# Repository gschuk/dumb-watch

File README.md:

# dumb-watch
Exercise Lab of Lecture Advanced PCB Design @ TU Darmstadt.

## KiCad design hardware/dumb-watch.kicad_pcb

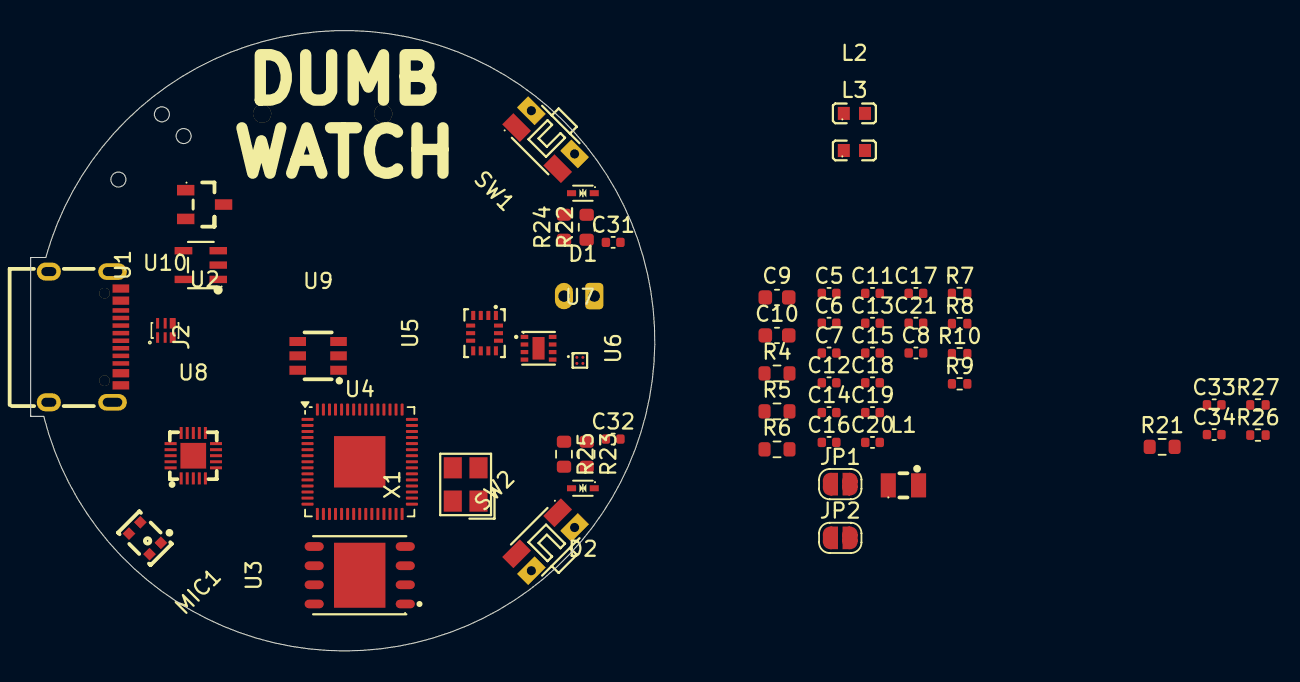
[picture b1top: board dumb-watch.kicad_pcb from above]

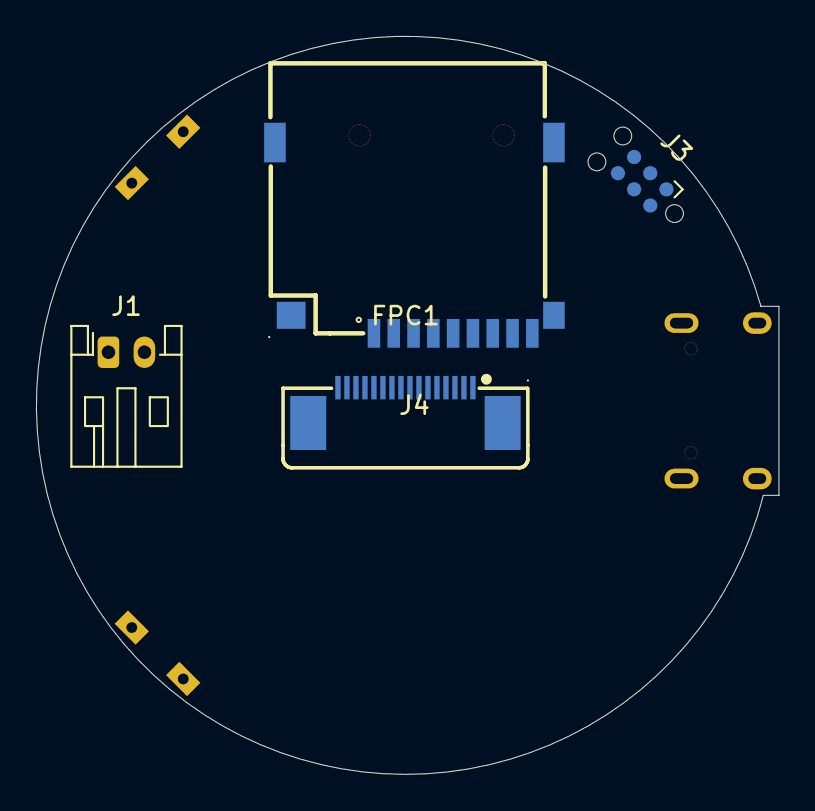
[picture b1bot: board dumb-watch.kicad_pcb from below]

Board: 2 copper layers, 41.2 x 41.0 mm, 61 parts (4 on the bottom side), 39 nets, no tracks yet.

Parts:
C5, C6: 10pF; C_0402_1005Metric
C7: 4.7µF 6.3V; C_0402_1005Metric
C8, C11, C12, C13, C14, C15, C16, C17, C18, C19, C20, C21, C31, C32, C33, C34: 100nF 25V; C_0402_1005Metric
C9, C10: 4.7µF 6.3V; C_0603_1608Metric
D1, D2: H3V3LD5B; SOD-523_L1.2-W0.8-LS1.6-BI
FPC1: FPC-0.5MM-16P-Slide-Lock-Top-Contact; FPC-SMD_16P-P0.50_AFC07-S16ECC-00
J1: Conn_01x02_Pin; JST_PH_S2B-PH-K_1x02_P2.00mm_Horizontal
J2: TYPE-C 16PIN 2MD; USB-C-SMD_TYPE-C-16PIN-2MD-073
J3: TagConnect_TC2030-NL; Tag-Connect_TC2030-IDC-NL_2x03_P1.27mm_Vertical
J4: TF PUSH; TF-SMD_TF-PUSH
JP1: Boot; SolderJumper-2_P1.3mm_Open_RoundedPad1.0x1.5mm
JP2: Reset; SolderJumper-2_P1.3mm_Open_RoundedPad1.0x1.5mm
L1: 3.3µH 2.1A; IND-SMD_L2.0-W1.6_AOTA-B201610S3R3-101-T
L2, L3: 120R @ 100MHz; L0603
MIC1: ZTS6117; MIC-SMD_4P-L2.8-W1.9-P1.84-TL_ZTS6117
R4, R21, R22, R23, R24, R25: 10k; R_0603_1608Metric
R5, R6: 1k; R_0603_1608Metric
R7, R8, R26, R27: 27; R_0402_1005Metric
R9: 33; R_0402_1005Metric
R10: 1k; R_0402_1005Metric
SW1, SW2: EVQP3401K; KEY-SMD_4P-L4.7-W3.5_EVQ9P
U1: MCP73831T-2ACI/OT; SOT-23-5_L3.0-W1.7-P0.95-LS2.8-BL
U2: XC6206P332MR; SOT-23-3_L2.9-W1.3-P1.90-LS2.4-BR-CW
U3: W25Q16JVZPIQ; WSON-8_L6.0-W5.0-P1.27-BL-EP
U4: RP2350A; QFN-60-1EP_7x7mm_P0.4mm_EP3.4x3.4mm
U5: BMI270; LGA-14_L3.0-W2.5-P0.50-BR
U6: PCF8563TDQ; DFN-8_L2.0-W2.0-P0.50-BL-EP1.5
U7: MMC5603NJ; FLIPCHIP-4_L0.8-W0.8-R2-C2-P0.40-TL
U8: ES8311; WQFN-20_L3.0-W3.0-P0.40-BL-EP1.7
U9: BCR421UW6Q-7; SOT-23-6_L2.9-W1.6-P0.95-LS2.8-BR
U10: RCLAMP0522P-ES; DFN-6_L1.6-W1.0-P0.50-BL
X1: ABM8-272-T3; CRYSTAL-SMD_4P-L3.2-W2.5-BL

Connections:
+1V1: C10.1, C12.1, C14.1, C16.1, L1.2, U4.6 (DVDD), U4.23 (DVDD), U4.39 (DVDD), U4.50 (VREG_FB)
+3.3V: U5.1 (SDO), U5.5 (VDDIO), U5.8 (VDD), U6.8 (VDD), U7.B1 (VDD)
+3V3: C8.1, C11.1, C13.1, C15.1, C17.1, C18.1, C19.1, C20.1, C21.1, C33.1, FPC1.12, FPC1.13, J3.1 (VCC), J4.4 (VDD), L2.1, L3.1, R4.1, R9.2, R24.1, R25.1, U2.3 (OUTPUT), U3.8 (VCC), U4.1 (IOVDD), U4.11 (IOVDD), U4.20 (IOVDD), U4.30 (IOVDD), U4.38 (IOVDD), U4.44 (ADC_AVDD), U4.45 (IOVDD), U4.53 (USB_OTP_VDD), U4.54 (QSPI_IOVDD), U8.3 (PVDD)
/Audio/AVDD: L3.2, U8.11 (AVDD)
/Audio/DVDD: L2.2, U8.4 (DVDD)
/HMI/BTN0: C31.1, R22.1
/HMI/BTN1: C32.1, R23.1
/HMI/LCD_BACKLIGHT: R21.1, U9.1 (EN)
/HMI/LCD_LEDK: FPC1.1, R27.1, U9.2 (OUT), U9.3 (OUT), U9.5 (OUT)
/MCU/FLASH_IO0: U3.5 (DI(IO0)), U4.57 (QSPI_SD0)
/MCU/FLASH_IO1: U3.2 (DO(IO1)), U4.59 (QSPI_SD1)
/MCU/FLASH_IO2: U3.3 (~WP(IO2)), U4.58 (QSPI_SD2)
/MCU/FLASH_IO3: U3.7 (HOLDorRESET#（IO3）), U4.55 (QSPI_SD3)
/MCU/FLASH_SCK: U3.6 (CLK), U4.56 (QSPI_SCLK)
/MCU/FLASH_~CS: R4.2, R5.1, U3.1 (~CS), U4.60 (~QSPI_SS)
/MCU/Sens_I2C.SCL: U5.13 (SCX), U6.6 (SCL), U7.A2 (SCL)
/MCU/Sens_I2C.SDA: U5.14 (SDX), U6.5 (SDA), U7.B2 (SDA)
/MCU/USB.DM: R7.1, U10.6 (NC)
/MCU/USB.DP: R8.1, U10.5 (NC)
/MCU/VREG_AVDD: C7.1, R9.1, U4.46 (VREG_AVDD)
/MCU/VREG_LX: L1.1, U4.48 (VREG_LX)
/MCU/~RST: J3.3 (~RESET), R6.1, U4.26 (RUN)
GND: C5.1, C6.2, C7.2, C8.2, C9.2, C10.2, C11.2, C12.2, C13.2, C14.2, C15.2, C16.2, C17.2, C18.2, C19.2, C20.2, C21.2, C31.2, C32.2, C33.2, C34.2, D1.1, D2.1, FPC1.3, FPC1.14, FPC1.15, FPC1.16, J1.2, J2.13 (EH), J2.14 (EH), J2.A1B12 (GND), J2.B1A12 (GND), J3.5 (GND), J4.6 (VSS), JP1.1 (A), JP2.1 (A), MIC1.2 (GND), MIC1.3 (GND), R21.2, R26.1, R27.2, SW1.4, SW2.2, U1.2 (VSS), U2.1 (GND), U3.4 (GND), U3.9 (EP), U4.47 (VREG_PGND), U4.61 (GND), U5.6 (GNDIO), U5.7 (GND), U6.4 (Vss), U7.A1 (VSA), U8.5 (DGND), U8.10 (AGND), U8.21 (EP), U9.4 (GND), U10.3 (GND), U10.4 (GND), X1.2 (GND), X1.4 (GND)
unnamed: C5.2, R10.1, X1.1
unnamed: D1.2, R22.2, R24.2, SW1.3
unnamed: D2.2, R23.2, R25.2, SW2.1
unnamed: J2.A7 (Dn1), J2.B7 (Dn2), U10.2 (IO2)
unnamed: J2.A6 (Dp1), J2.B6 (Dp2), U10.1 (IO1)
unnamed: J3.4 (SWCLK), U4.24 (SWCLK)
unnamed: J3.2 (SWDIO), U4.25 (SWDIO)
unnamed: JP1.2 (B), R5.2
unnamed: JP2.2 (B), R6.2
unnamed: R7.2, U4.51 (USB_DM)
unnamed: R8.2, U4.52 (USB_DP)
unnamed: C6.1, U4.21 (XIN), X1.3
unnamed: R10.2, U4.22 (XOUT)
unnamed: R26.2, U9.6 (REXT)
VBAT: C9.1, C34.1, FPC1.2, J1.1, U1.3 (VBAT), U2.2 (INPUT), U4.49 (VREG_VIN)
VBUS: J2.A4B9 (VBUS), J2.B4A9 (VBUS), U1.4 (VDD)
